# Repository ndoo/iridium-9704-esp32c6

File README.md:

# Iridium 9704 ESP32C6

A basic and incomplete portable Iridium Messaging Transport communicator.

## Images

Rendered with [kicad-render](https://github.com/linalinn/kicad-render)

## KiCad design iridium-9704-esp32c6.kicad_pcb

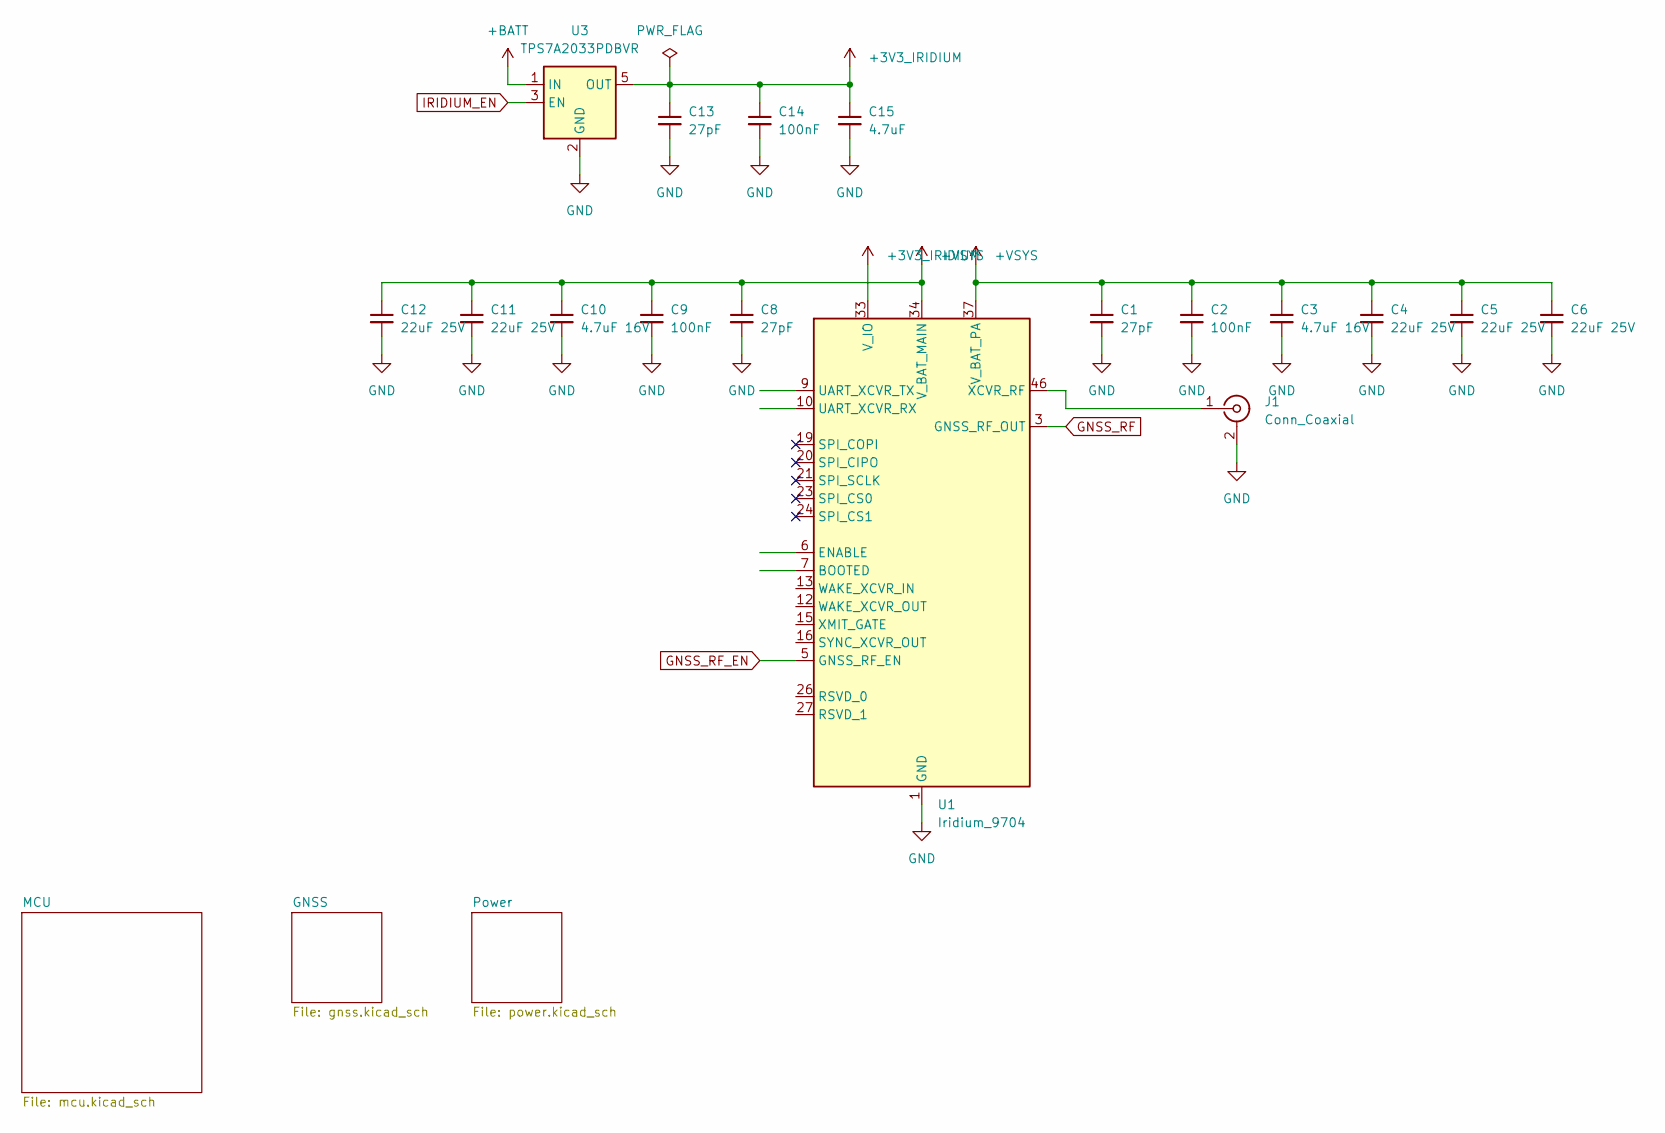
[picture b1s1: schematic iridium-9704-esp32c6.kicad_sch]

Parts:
C1, C8, C13: 27pF; C_0402_1005Metric; LCSC C1557
C2, C9, C14: 100nF; C_0402_1005Metric; LCSC C1525
C3, C10: 4.7uF 16V; C_0603_1608Metric; LCSC C19666
C4, C5, C6, C11, C12: 22uF 25V; C_0805_2012Metric; LCSC C45783
C15: 4.7uF; C_0603_1608Metric; LCSC C19666
J1: Conn_Coaxial; SMA_Samtec_SMA-J-P-H-ST-EM1_EdgeMount; LCSC C496550
U1: Iridium_9704
U3: TPS7A2033PDBVR; SOT-23-5; LCSC C2862740

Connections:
+3V3_IRIDIUM: C13.1, C14.1, C15.1, U1.33 (V_IO), U3.5 (OUT)
+BATT: U3.1 (IN); also elsewhere on the board
+VSYS: C1.1, C2.1, C3.1, C4.1, C5.1, C6.1, C8.1, C9.1, C10.1, C11.1, C12.1, U1.34 (V_BAT_MAIN), U1.35 (V_BAT_MAIN), U1.36 (V_BAT_MAIN), U1.37 (V_BAT_PA), U1.38 (V_BAT_PA), U1.39 (V_BAT_PA), U1.40 (V_BAT_PA), U1.41 (V_BAT_PA), U1.42 (V_BAT_PA), U1.43 (V_BAT_PA), U1.44 (V_BAT_PA)
GND: C1.2, C2.2, C3.2, C4.2, C5.2, C6.2, C8.2, C9.2, C10.2, C11.2, C12.2, C13.2, C14.2, C15.2, J1.2 (Ext), U1.1 (GND), U1.2 (GND), U1.4 (GND), U1.8 (GND), U1.11 (GND), U1.14 (GND), U1.17 (GND), U1.18 (GND), U1.22 (GND), U1.25 (GND), U1.31 (GND), U1.32 (GND), U1.45 (GND), U1.47 (GND), U1.48 (GND), U1.60 (GND), U1.61 (GND), U1.62 (GND), U1.63 (GND), U1.64 (GND), U1.65 (GND), U1.66 (GND), U1.75 (GND), U1.76 (GND), U1.77 (GND), U1.78 (GND), U1.79 (GND), U1.80 (GND), U3.2 (GND); also elsewhere on the board
GNSS_RF: U1.3 (GNSS_RF_OUT); also elsewhere on the board
GNSS_RF_EN: U1.5 (GNSS_RF_EN); also elsewhere on the board
IRIDIUM_EN: U3.3 (EN)
unnamed: J1.1 (In), U1.46 (XCVR_RF)

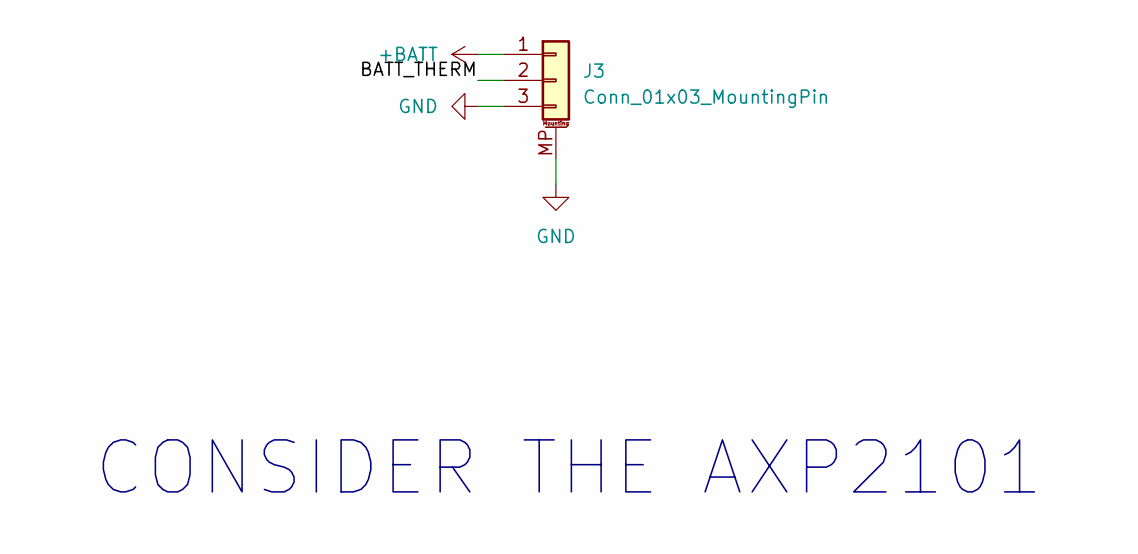
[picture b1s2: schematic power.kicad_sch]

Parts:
J3: Conn_01x03_MountingPin; Molex_PicoBlade_53261-0371_1x03-1MP_P1.25mm_Horizontal; LCSC C7433469

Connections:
+BATT: J3.1; also elsewhere on the board
/Power/BATT_THERM: J3.2
GND: J3.3, J3.MP (MountPin); also elsewhere on the board

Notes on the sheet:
CONSIDER THE AXP2101

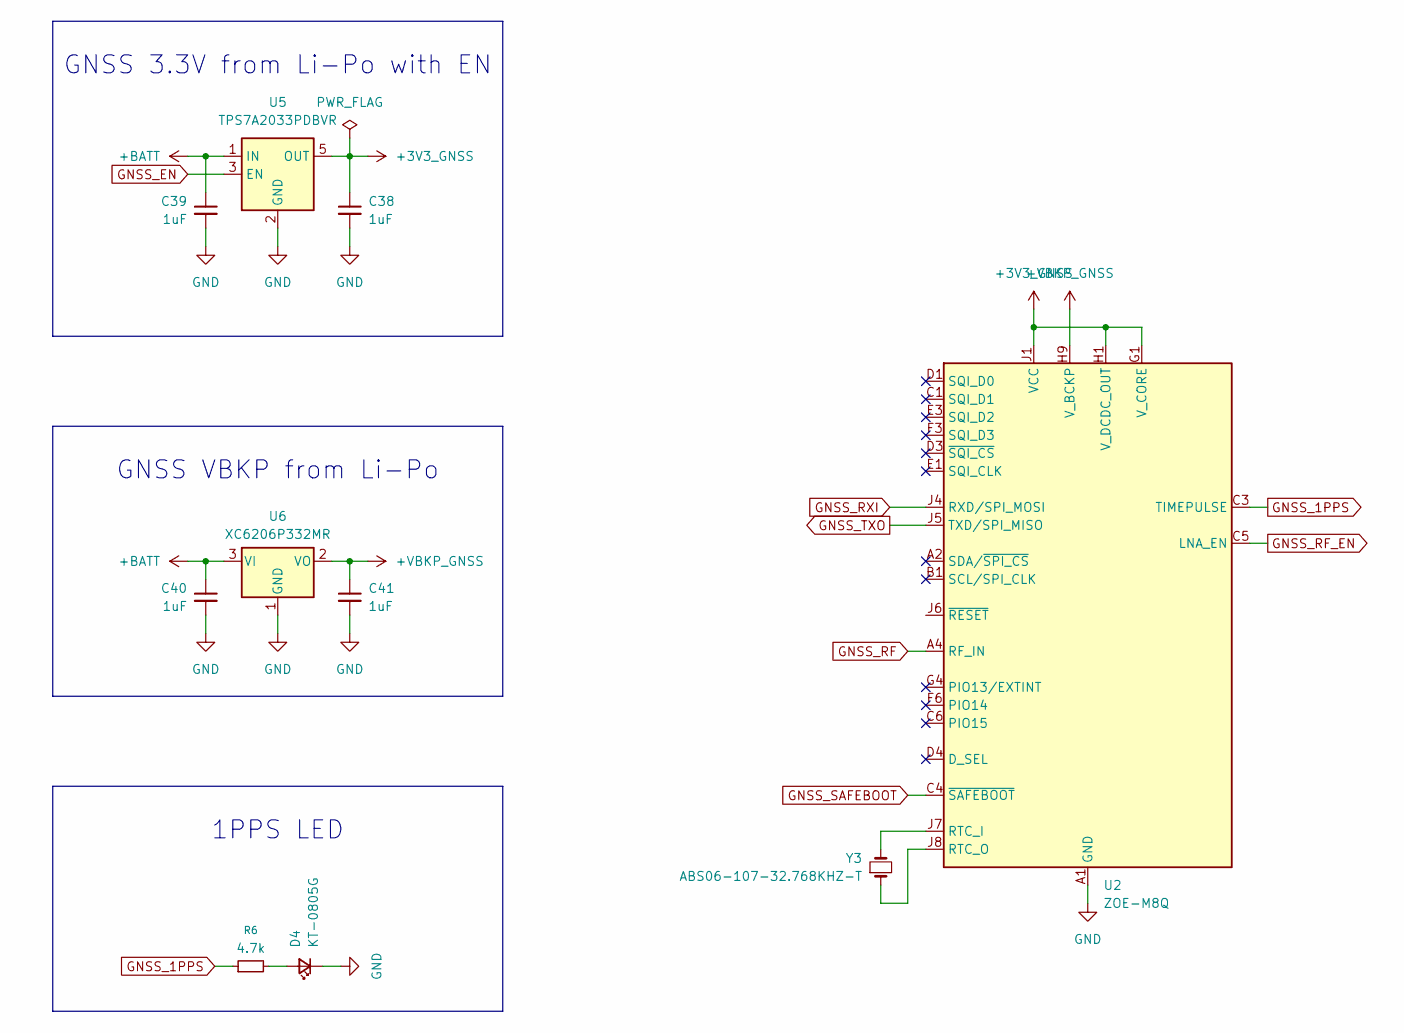
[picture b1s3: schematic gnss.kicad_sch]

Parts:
C38, C39, C40, C41: 1uF; C_0402_1005Metric; LCSC C52923
D4: KT-0805G; LED_0805_2012Metric; LCSC C2297
R6: 4.7k; R_0402_1005Metric; LCSC C25900
U2: ZOE-M8Q; ublox_ZOE_M8; LCSC C7398634
U5: TPS7A2033PDBVR; SOT-23-5; LCSC C2862740
U6: XC6206P332MR; SOT-23-3; LCSC C5446
Y3: ABS06-107-32.768KHZ-T; Crystal_SMD_2012-2Pin_2.0x1.2mm; LCSC C276418

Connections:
+3V3_GNSS: C38.1, U2.G1 (V_CORE), U2.H1 (V_DCDC_OUT), U2.J1 (VCC), U2.J2 (VCC), U5.5 (OUT)
+BATT: C39.1, C40.1, U5.1 (IN), U6.3 (VI); also elsewhere on the board
+VBKP_GNSS: C41.1, U2.H9 (V_BCKP), U6.2 (VO)
GND: C38.2, C39.2, C40.2, C41.2, D4.1 (K), U2.A1 (GND), U2.A3 (GND), U2.A5 (GND), U2.A7 (GND), U2.A8 (GND), U2.A9 (GND), U2.B9 (GND), U2.C7 (GND), U2.C9 (GND), U2.D6 (GND), U2.D9 (GND), U2.E7 (GND), U2.F7 (GND), U2.G3 (GND), U2.G6 (GND), U2.G7 (GND), U2.J3 (GND), U2.J9 (GND), U5.2 (GND), U6.1 (GND); also elsewhere on the board
GNSS_1PPS: R6.1, U2.C3 (TIMEPULSE)
GNSS_EN: U5.3 (EN)
GNSS_RF: U2.A4 (RF_IN); also elsewhere on the board
GNSS_RF_EN: U2.C5 (LNA_EN); also elsewhere on the board
GNSS_RXI: U2.J4 (RXD/SPI_MOSI)
GNSS_SAFEBOOT: U2.C4 (~SAFEBOOT)
GNSS_TXO: U2.J5 (TXD/SPI_MISO)
unnamed: D4.2 (A), R6.2
unnamed: U2.J7 (RTC_I), Y3.2
unnamed: U2.J8 (RTC_O), Y3.1

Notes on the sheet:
GNSS VBKP from Li-Po
GNSS 3.3V from Li-Po with EN
1PPS LED

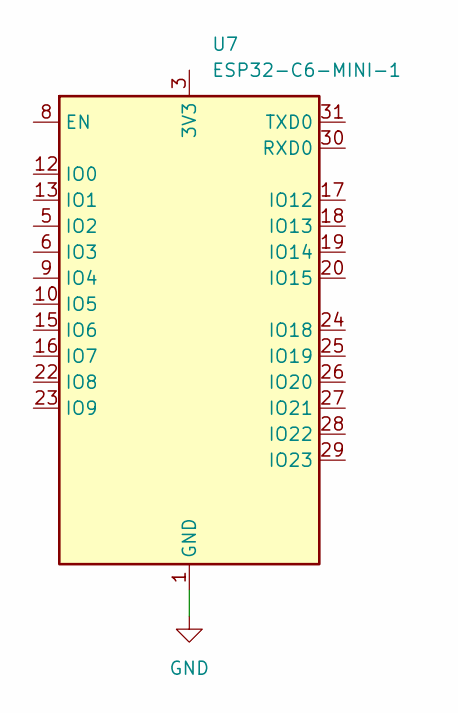
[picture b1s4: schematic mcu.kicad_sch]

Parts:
U7: ESP32-C6-MINI-1; LCSC C5736265

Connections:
GND: U7.1 (GND), U7.2 (GND), U7.11 (GND), U7.14 (GND), U7.36 (GND), U7.37 (GND), U7.38 (GND), U7.39 (GND), U7.40 (GND), U7.41 (GND), U7.42 (GND), U7.43 (GND), U7.44 (GND), U7.45 (GND), U7.46 (GND), U7.47 (GND), U7.48 (GND), U7.49 (GND), U7.50 (GND), U7.51 (GND), U7.52 (GND), U7.53 (GND); also elsewhere on the board

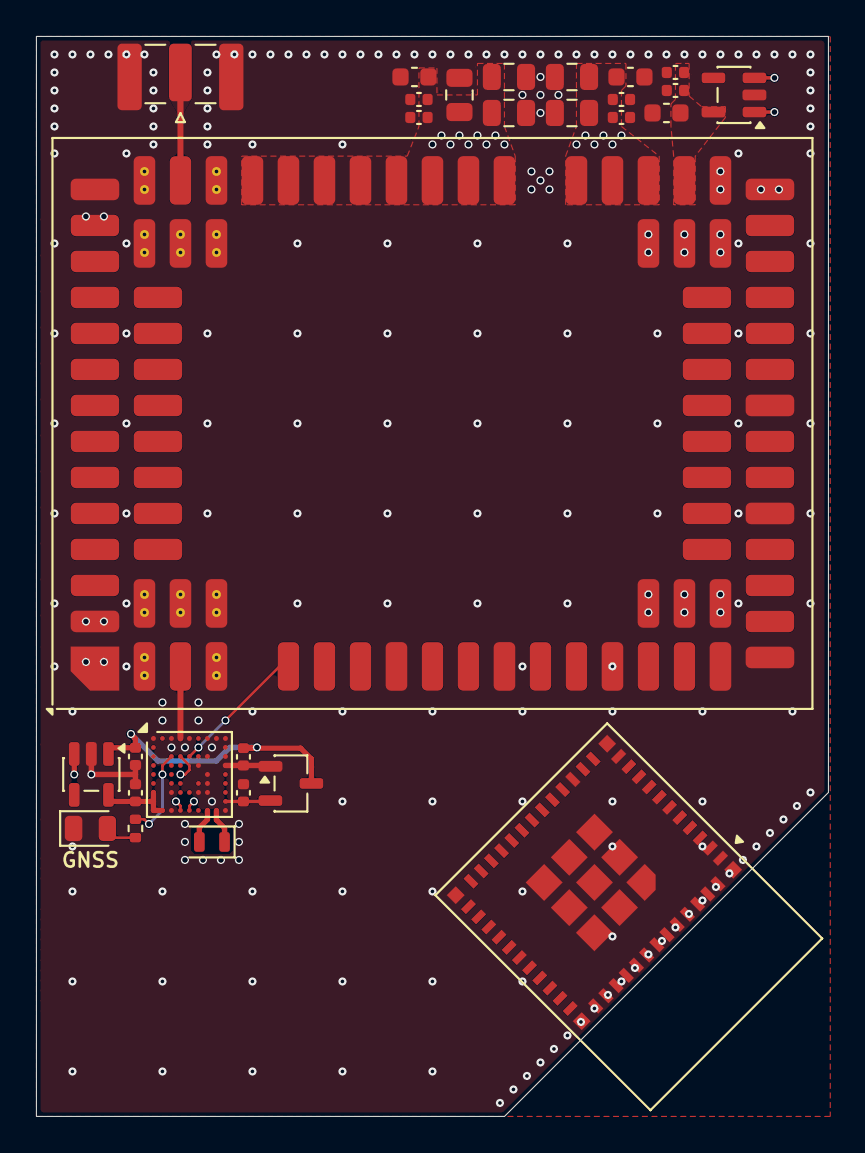
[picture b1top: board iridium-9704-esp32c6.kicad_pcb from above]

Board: 2 copper layers, 44.0 x 60.0 mm, 29 parts (1 on the bottom side), 13 nets.
